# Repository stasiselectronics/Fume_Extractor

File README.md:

# Fume Extractor
This repository contains all the design file for a battery powered fume extractor for soldering.

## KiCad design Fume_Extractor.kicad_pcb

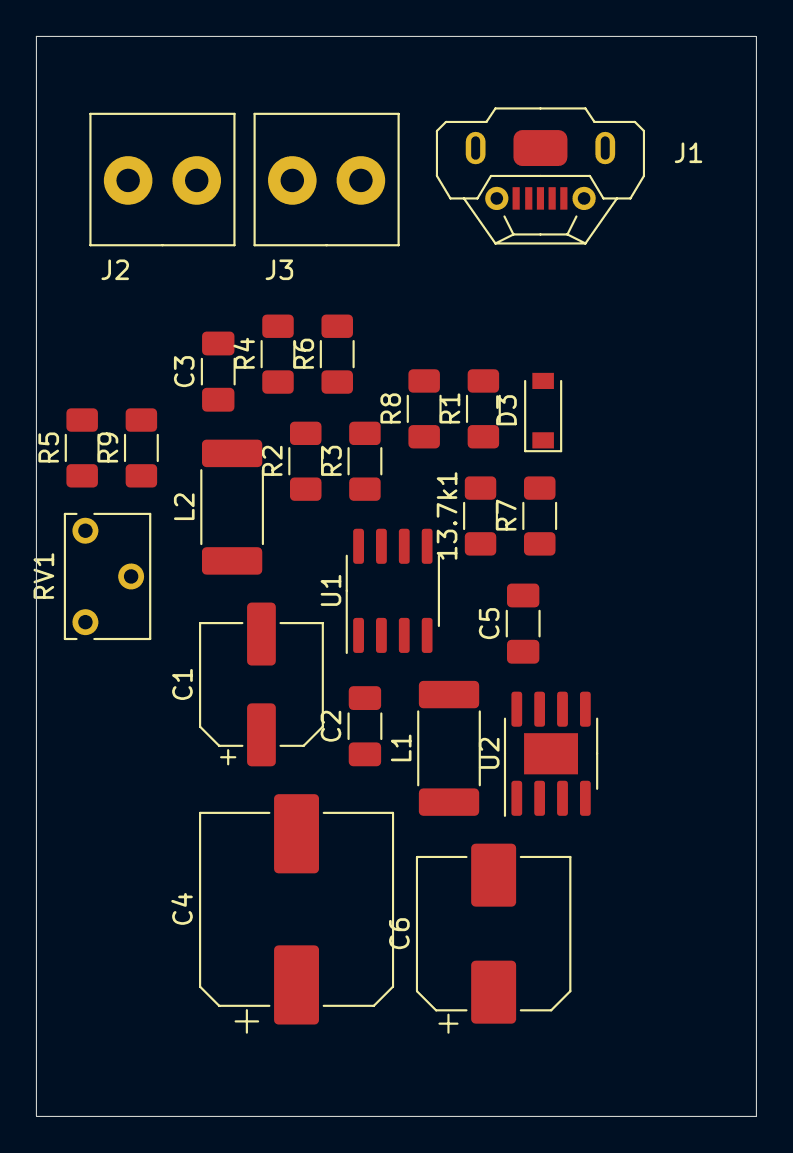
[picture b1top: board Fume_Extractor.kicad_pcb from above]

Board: 2 copper layers, 40.0 x 60.0 mm, 25 parts (0 on the bottom side), 15 nets, no tracks yet.

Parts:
13.7k1: R2; R_1206_3216Metric_Pad1.30x1.75mm_HandSolder
C1: 100µF; CP_Elec_6.3x5.3
C2, C5: 10uF; C_1206_3216Metric_Pad1.33x1.80mm_HandSolder
C3: 1.5nF ±10% 50V X7R 1206; C_1206_3216Metric_Pad1.33x1.80mm_HandSolder
C4: 330uF ±20% 50V; CP_Elec_10x12.5
C6: 100uF ±20% 50V; CP_Elec_8x10
D3: 40V 1A 450mV @ 1A; D_SOD-123
J1: USB_B_Micro; U-F-M5DD-Y-L
J2, J3: Conn_01x02; WJ124-3.81-2P
L1: 150uH ±10% 6*8 Radial Inductor; L_2512_6332Metric_Pad1.52x3.35mm_HandSolder
L2: 1uH ±20% 3.29A 59mΩ SMD,2.5x2x1.2mm; L_2512_6332Metric_Pad1.52x3.35mm_HandSolder
R1: R1; R_1206_3216Metric_Pad1.30x1.75mm_HandSolder
R2: 0.22 R; R_1206_3216Metric_Pad1.30x1.75mm_HandSolder
R3, R6: 10k; R_1206_3216Metric_Pad1.30x1.75mm_HandSolder
R4: 180R; R_1206_3216Metric_Pad1.30x1.75mm_HandSolder
R5: 48k; R_1206_3216Metric_Pad1.30x1.75mm_HandSolder
R7: 118k; R_1206_3216Metric_Pad1.30x1.75mm_HandSolder
R8: RProg; R_1206_3216Metric_Pad1.30x1.75mm_HandSolder
R9: 508.064k; R_1206_3216Metric_Pad1.30x1.75mm_HandSolder
RV1: 500M; Potentiometer_Bourns_3266W_Vertical
U1: SP34063AEN; SOIC-8_3.9x4.9mm_P1.27mm
U2: TP4056; SOIC-8-1EP_3.9x4.9mm_P1.27mm_EP2.29x3mm

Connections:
+5V: C2.1, J1.1, R1.2, R3.2, R6.2, U2.4, U2.8
+12V: C6.1, J3.1, L2.2
GND: 13.7k1.1, C1.2, C2.2, C3.2, C4.2, C5.2, C6.2, J1.5, J1.6, J2.2, J3.2, R8.1, U1.2, U1.4, U2.3
unnamed: 13.7k1.2, R7.2, U1.5
unnamed: C3.1, U1.3
unnamed: C4.1, D3.1, L2.1, R7.1
unnamed: D3.2, L1.2, U1.1
unnamed: R1.1, U2.1
unnamed: L1.1, R2.1, R4.2, U1.6, U1.7
unnamed: R4.1, U1.8
unnamed: R5.1, R9.2, RV1.1
unnamed: R8.2, U2.2
unnamed: R9.1, RV1.2
VBATT: C5.1, J2.1, U2.5
VCC: C1.1, R2.2

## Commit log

2021-04-21 add template files
2021-04-21 Rename Project Files
2021-04-21 add a4 template page for schematics
2021-04-21 Add licence
2021-04-21 Add new symbols
2021-04-21 add most schematic components
2021-04-21 Add footprints and begin placing components
2021-04-21 add datasheet references
2021-05-10 update schematic
2021-05-11 Major schematic and layout updates
